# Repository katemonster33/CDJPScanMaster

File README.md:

# CDJPScanMaster

A modern re-design of the Chrysler DRBIII scan tool. This tool, once complete, should be able to connect to 1996(ish) to 2007 vehicles previously supported by the DRB. Most of the key-on-engine-off actuator tests (injector coil and et cetera) should be easy to implement, but the system tests (like Injector Kill) will need special attention to get working.

The user interface for the DRBDBReader (library for interpreting the database.mem) has a UI, but is mostly for my own testing. This library is mostly complete. Initial work on this goes to MWisBest. 

Currently this repo contains a scan tool application, and the beginnings of my new circuit board. This application will not load without the database.mem file found on the DRB III or in the folder of the DRB Emulator. Apparently there's a version of this database shipped with StarScan which theoretically could work, but it's never been tested. The app will soon undergo a complete overhaul, however, as I design a new circuit board which will eventually support Bluetooth, and which will connect to an app for Android and (eventually) PC. This circuit will support ISO9141/KWP2000, SCI(A and B configuration, ECM and TCM), J1850VPW and CCD. 

Credit goes to MWisBest for his initial work on DRBDBReader.

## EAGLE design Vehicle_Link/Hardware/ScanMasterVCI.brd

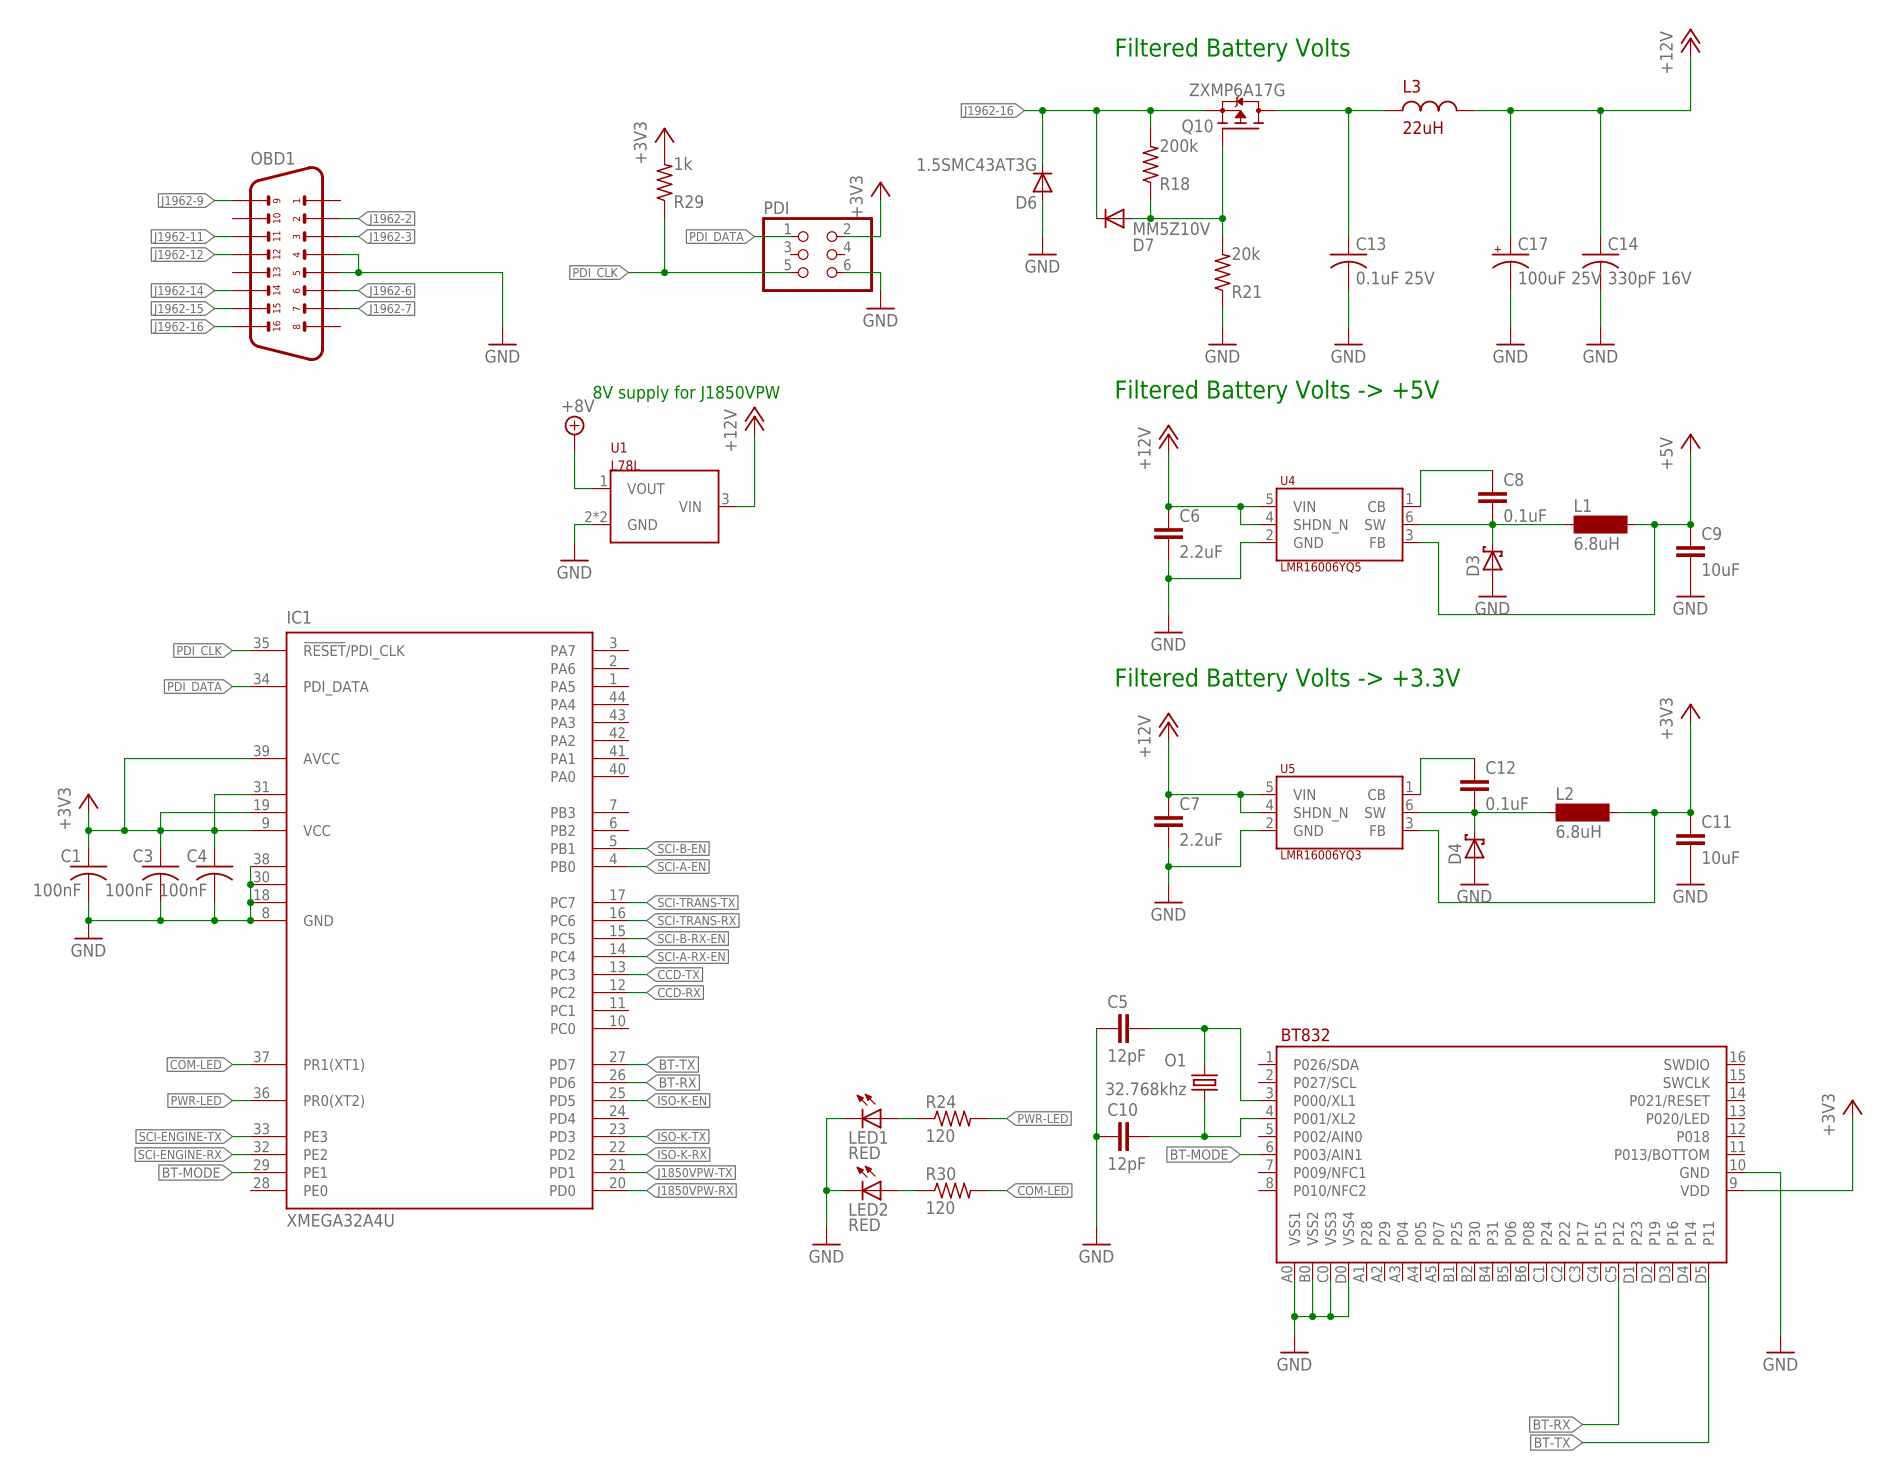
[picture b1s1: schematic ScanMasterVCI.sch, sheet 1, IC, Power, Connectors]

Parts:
C1, C3, C4: 100nF; C0402
C5, C10: 12pF; 0603
C6, C7: 2.2uF; 1206
C8, C12: 0.1uF; 0603
C9, C11: 10uF; 0603
C13: 0.1uF 25V; C0603
C14: 330pF 16V; C0603
C17: 100uF 25V; CPOL-RADIAL-2.5MM-6.5MM
D3, D4: SM5817PL; SOD123FL
D6: 1.5SMC43AT3G; SMC
D7: MM5Z10V; SOD523
IC1: XMEGA32A4U; MLF44-TH
L1, L2: 6.8uH; SM-1206
L3: 22uH; L0603
LED1, LED2: RED; CHIP-LED0603
O1: 32.768khz; FC-135
OBD1: OBD2_OBD2_90; OBD2
PDI: PINHD-2X3; 2X03
Q10: ZXMP6A17G; SOT223
R18: 200k; R0603
R21: 20k; R0603
R24, R30: 120; R0603
R29: 1k; R0603
U1: L78L; SOT89
U4: LMR16006YQ5; SOT6
U5: LMR16006YQ3; SOT6
U6: BT832A

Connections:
+3V3: C1.1, C3.1, C4.1, C11.1, IC1.9 (VCC), IC1.19 (VCC1), IC1.31 (VCC2), IC1.39 (AVCC), L2.2, PDI.2, R29.2, U5.3 (FB), U6.9 (VDD); also elsewhere on the board
+5V: C9.1, L1.2, U4.3 (FB); also elsewhere on the board
+8V: U1.1 (VOUT); also elsewhere on the board
+12V: C6.1, C7.1, C14.1, C17.1 (+), L3.2, U1.3 (VIN), U4.4 (SHDN_N), U4.5 (VIN), U5.4 (SHDN_N), U5.5 (VIN); also elsewhere on the board
BT-MODE: IC1.29 (PE1), U6.6 (P003/AIN1)
BT-RX: IC1.26 (PD6), U6.C5 (P12)
BT-TX: IC1.27 (PD7), U6.D5 (P11)
CCD-RX: IC1.12 (PC2); also elsewhere on the board
CCD-TX: IC1.13 (PC3); also elsewhere on the board
COM-LED: IC1.37 (PR1(XT1)), R30.2
GND: C1.2, C3.2, C4.2, C5.1, C6.2, C7.2, C9.2, C10.1, C11.2, C13.2, C14.2, C17.2 (-), D3.A, D4.A, D6.A, IC1.8 (GND), IC1.18 (GND1), IC1.30 (GND2), IC1.38 (GND3), LED1.C, LED2.C, OBD1.4, OBD1.5, PDI.6, R21.1, U1.2 (GND), U1.2@1 (GND), U4.2 (GND), U5.2 (GND), U6.10 (GND), U6.A0 (VSS1), U6.B0 (VSS2), U6.C0 (VSS3), U6.D0 (VSS4); also elsewhere on the board
ISO-K-EN: IC1.25 (PD5); also elsewhere on the board
ISO-K-RX: IC1.22 (PD2); also elsewhere on the board
ISO-K-TX: IC1.23 (PD3); also elsewhere on the board
J1850VPW-RX: IC1.20 (PD0); also elsewhere on the board
J1850VPW-TX: IC1.21 (PD1); also elsewhere on the board
J1962-2: OBD1.2; also elsewhere on the board
J1962-3: OBD1.3; also elsewhere on the board
J1962-6: OBD1.6; also elsewhere on the board
J1962-7: OBD1.7; also elsewhere on the board
J1962-9: OBD1.9; also elsewhere on the board
J1962-11: OBD1.11; also elsewhere on the board
J1962-12: OBD1.12; also elsewhere on the board
J1962-14: OBD1.14; also elsewhere on the board
J1962-15: OBD1.15; also elsewhere on the board
J1962-16: D6.C, D7.C, OBD1.16, Q10.3 (S), R18.2
unnamed: LED1.A, R24.1
unnamed: C8.1, U4.1 (CB)
unnamed: C8.2, D3.C, L1.1, U4.6 (SW)
unnamed: C12.2, D4.C, L2.1, U5.6 (SW)
unnamed: C12.1, U5.1 (CB)
unnamed: C5.2, O1.2, U6.3 (P000/XL1)
unnamed: C13.1, L3.1, Q10.2 (D), Q10.4 (D)
unnamed: D7.A, Q10.1 (G), R18.1, R21.2
unnamed: C10.2, O1.1, U6.4 (P001/XL2)
unnamed: LED2.A, R30.1
PDI_CLK: IC1.35 (!RESET!/PDI_CLK), PDI.5, R29.1
PDI_DATA: IC1.34 (PDI_DATA), PDI.1
PWR-LED: IC1.36 (PR0(XT2)), R24.2
SCI-A-EN: IC1.4 (PB0); also elsewhere on the board
SCI-A-RX-EN: IC1.14 (PC4); also elsewhere on the board
SCI-B-EN: IC1.5 (PB1); also elsewhere on the board
SCI-B-RX-EN: IC1.15 (PC5)
SCI-ENGINE-RX: IC1.32 (PE2); also elsewhere on the board
SCI-ENGINE-TX: IC1.33 (PE3); also elsewhere on the board
SCI-TRANS-RX: IC1.16 (PC6); also elsewhere on the board
SCI-TRANS-TX: IC1.17 (PC7); also elsewhere on the board

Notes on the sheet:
Filtered Battery Volts
Filtered Battery Volts -> +5V
Filtered Battery Volts -> +3.3V
8V supply for J1850VPW

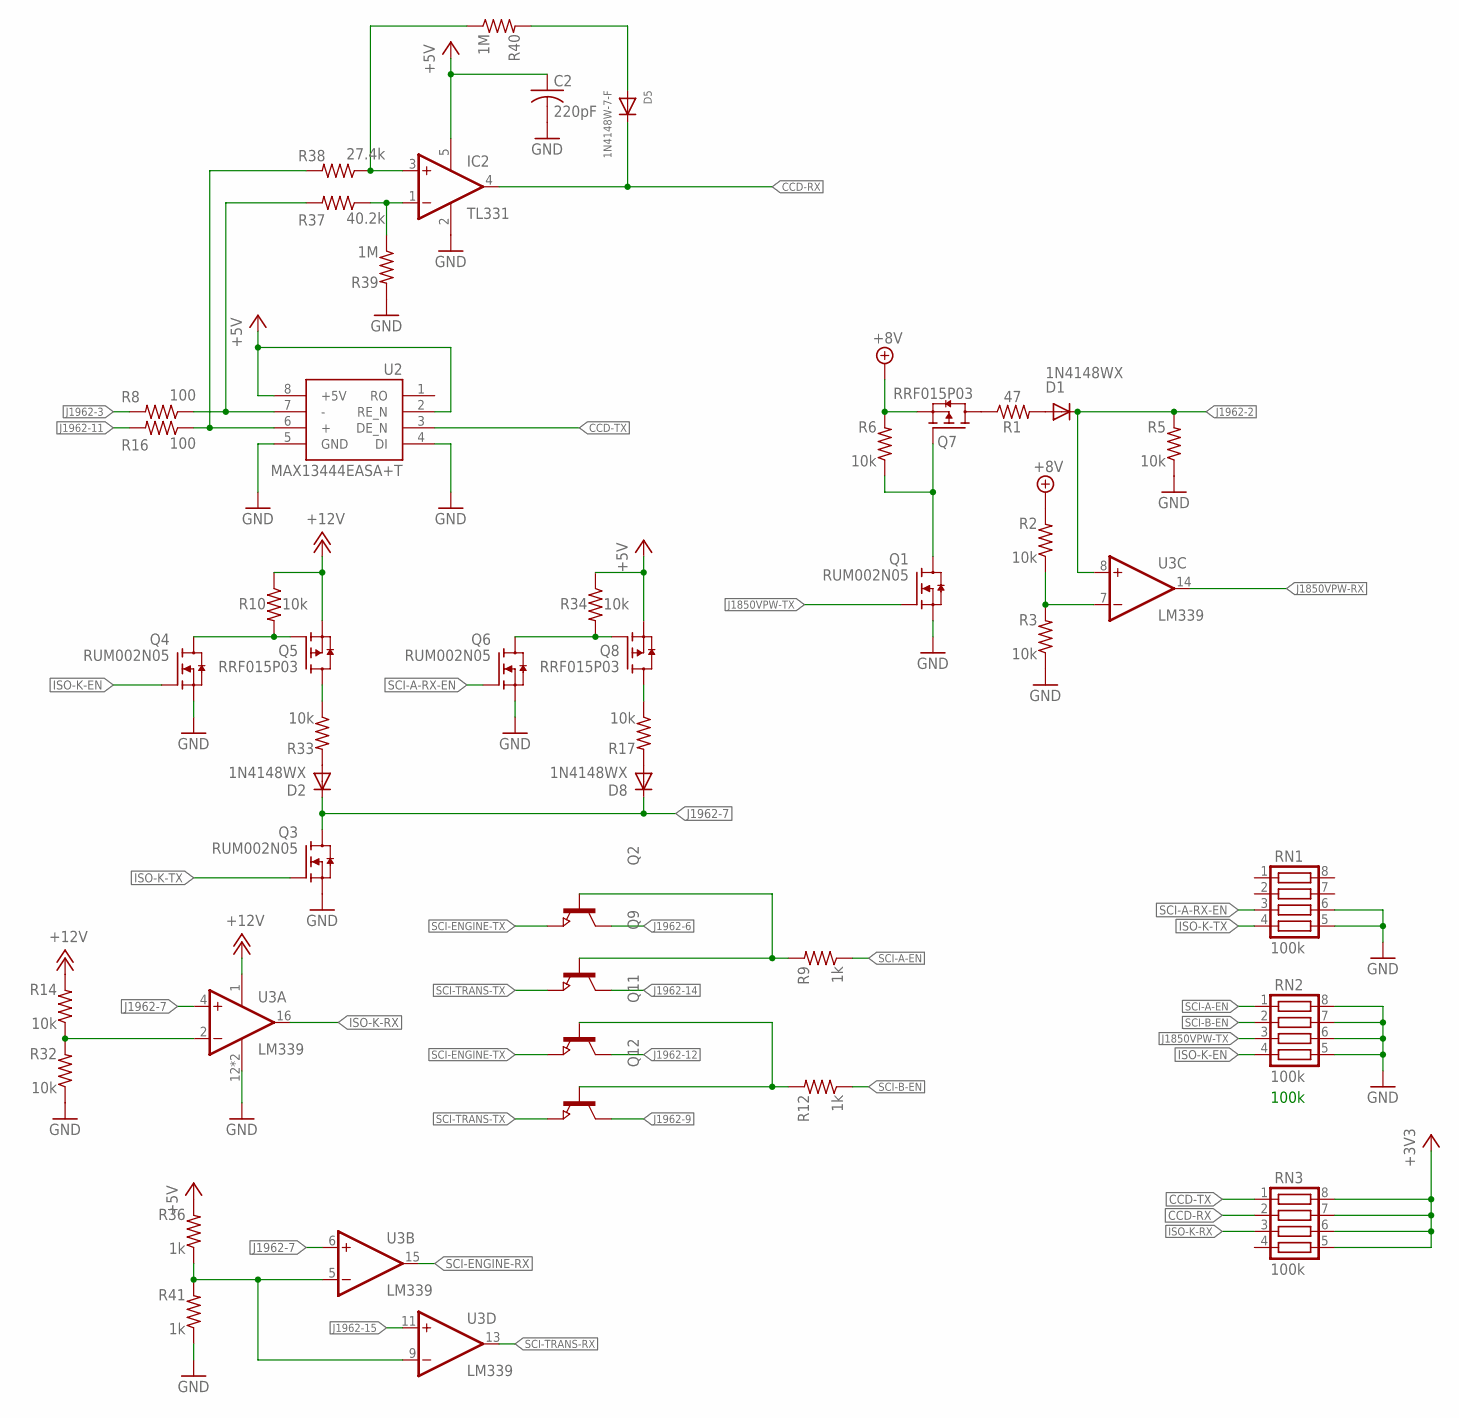
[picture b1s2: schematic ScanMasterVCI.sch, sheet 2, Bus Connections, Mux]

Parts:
C2: 220pF; C0603
D1, D2, D8: 1N4148WX; SOD323-R
D5: 1N4148W-7-F; SOD123FL
IC2: TL331; DBV-R-PDSO-G5
Q1, Q3, Q4, Q6: RUM002N05; EMT3
Q2, Q9, Q11, Q12: NPN-TRANSISTOR_SOT23; SOT23
Q5, Q7, Q8: RRF015P03; SOT323
R1: 47; R0603
R2, R3, R5, R6, R10, R14, R17, R32, R33, R34: 10k; R0603
R8, R16: 100; R0603
R9, R12, R36, R41: 1k; R0603
R37: 40.2k; R0603
R38: 27.4k; R0603
R39, R40: 1M; R0603
RN1, RN2, RN3: 100k; CTS742C083
U2: MAX13444EASA+T; SO08
U3: LM339; QFN16

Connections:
+3V3: RN3.5, RN3.6, RN3.7, RN3.8; also elsewhere on the board
+5V: C2.1, IC2.5 (V+), Q8.2 (S), R34.1, R36.2, U2.2 (RE_N), U2.8 (+5V); also elsewhere on the board
+8V: Q7.2 (S), R2.2, R6.2; also elsewhere on the board
+12V: Q5.2 (S), R10.1, R14.2, U3.1 (V+); also elsewhere on the board
CCD-RX: D5.C, IC2.4 (OUT), RN3.2; also elsewhere on the board
CCD-TX: RN3.1, U2.3 (DE_N); also elsewhere on the board
GND: C2.2, IC2.2 (GND), Q1.2 (S), Q3.2 (S), Q4.2 (S), Q6.2 (S), R3.1, R5.1, R32.1, R39.2, R41.1, RN1.5, RN1.6, RN2.5, RN2.6, RN2.7, RN2.8, U2.4 (DI), U2.5 (GND), U3.12 (V-), U3.PAD (V-); also elsewhere on the board
ISO-K-EN: Q4.1 (G), RN2.4; also elsewhere on the board
ISO-K-RX: RN3.3, U3.16 (OUT); also elsewhere on the board
ISO-K-TX: Q3.1 (G), RN1.4; also elsewhere on the board
J1850VPW-RX: U3.14 (OUT); also elsewhere on the board
J1850VPW-TX: Q1.1 (G), RN2.3; also elsewhere on the board
J1962-2: D1.C, R5.2, U3.8 (+IN); also elsewhere on the board
J1962-3: R8.2; also elsewhere on the board
J1962-6: Q2.3 (C); also elsewhere on the board
J1962-7: D2.C, D8.C, Q3.3 (D), U3.4 (+IN), U3.6 (+IN); also elsewhere on the board
J1962-9: Q12.3 (C); also elsewhere on the board
J1962-11: R16.2; also elsewhere on the board
J1962-12: Q11.3 (C); also elsewhere on the board
J1962-14: Q9.3 (C); also elsewhere on the board
J1962-15: U3.11 (+IN); also elsewhere on the board
unnamed: Q2.1 (B), Q9.1 (B), R9.2
unnamed: Q4.3 (D), Q5.1 (G), R10.2
unnamed: Q11.1 (B), Q12.1 (B), R12.2
unnamed: R36.1, R41.2, U3.5 (-IN), U3.9 (-IN)
unnamed: R14.1, R32.2, U3.2 (-IN)
unnamed: Q7.3 (D), R1.1
unnamed: D2.A, R33.2
unnamed: D8.A, R17.2
unnamed: Q5.3 (D), R33.1
unnamed: Q6.3 (D), Q8.1 (G), R34.2
unnamed: Q1.3 (D), Q7.1 (G), R6.1
unnamed: D1.A, R1.2
unnamed: Q8.3 (D), R17.1
unnamed: R16.1, R38.2, U2.6 (+)
unnamed: IC2.1 (-IN), R37.1, R39.1
unnamed: IC2.3 (+IN), R38.1, R40.1
unnamed: D5.A, R40.2
unnamed: R2.1, R3.2, U3.7 (-IN)
unnamed: R8.1, R37.2, U2.7 (-)
SCI-A-EN: R9.1, RN2.1; also elsewhere on the board
SCI-A-RX-EN: Q6.1 (G), RN1.3; also elsewhere on the board
SCI-B-EN: R12.1, RN2.2; also elsewhere on the board
SCI-ENGINE-RX: U3.15 (OUT); also elsewhere on the board
SCI-ENGINE-TX: Q2.2 (E), Q11.2 (E); also elsewhere on the board
SCI-TRANS-RX: U3.13 (OUT); also elsewhere on the board
SCI-TRANS-TX: Q9.2 (E), Q12.2 (E); also elsewhere on the board

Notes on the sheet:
100k

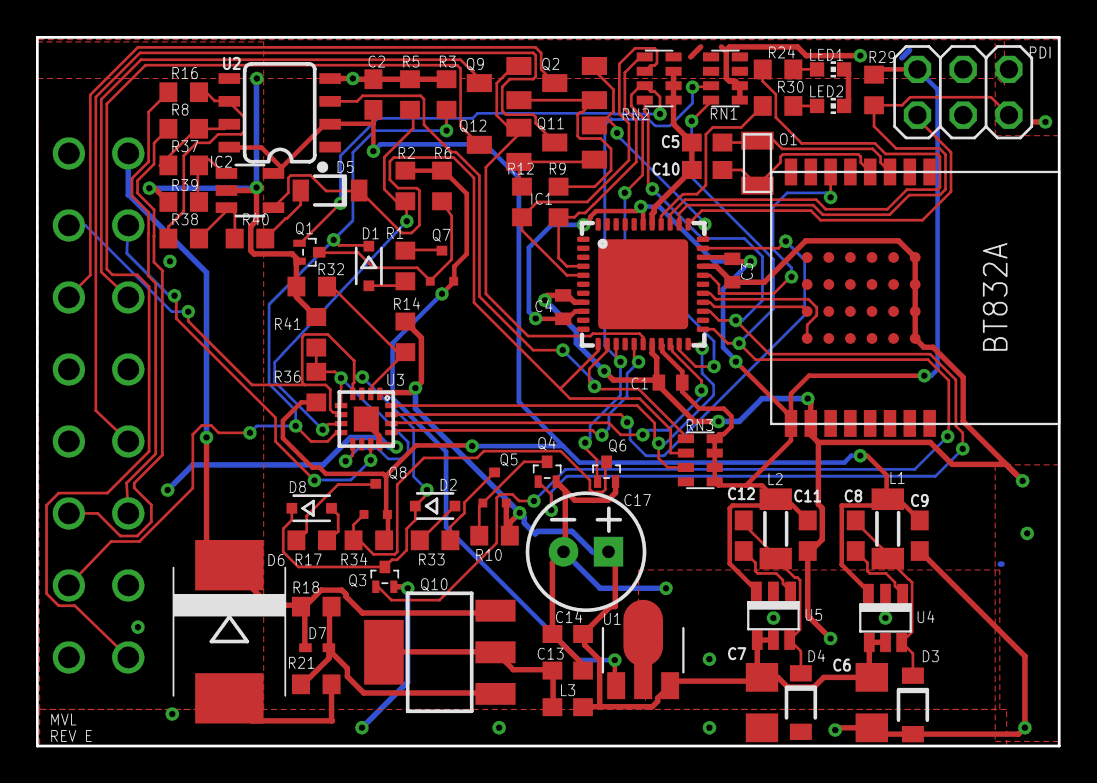
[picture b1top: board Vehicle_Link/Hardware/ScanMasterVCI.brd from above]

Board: 2 copper layers, 56.8 x 39.4 mm, 80 parts (0 on the bottom side), 65 nets.

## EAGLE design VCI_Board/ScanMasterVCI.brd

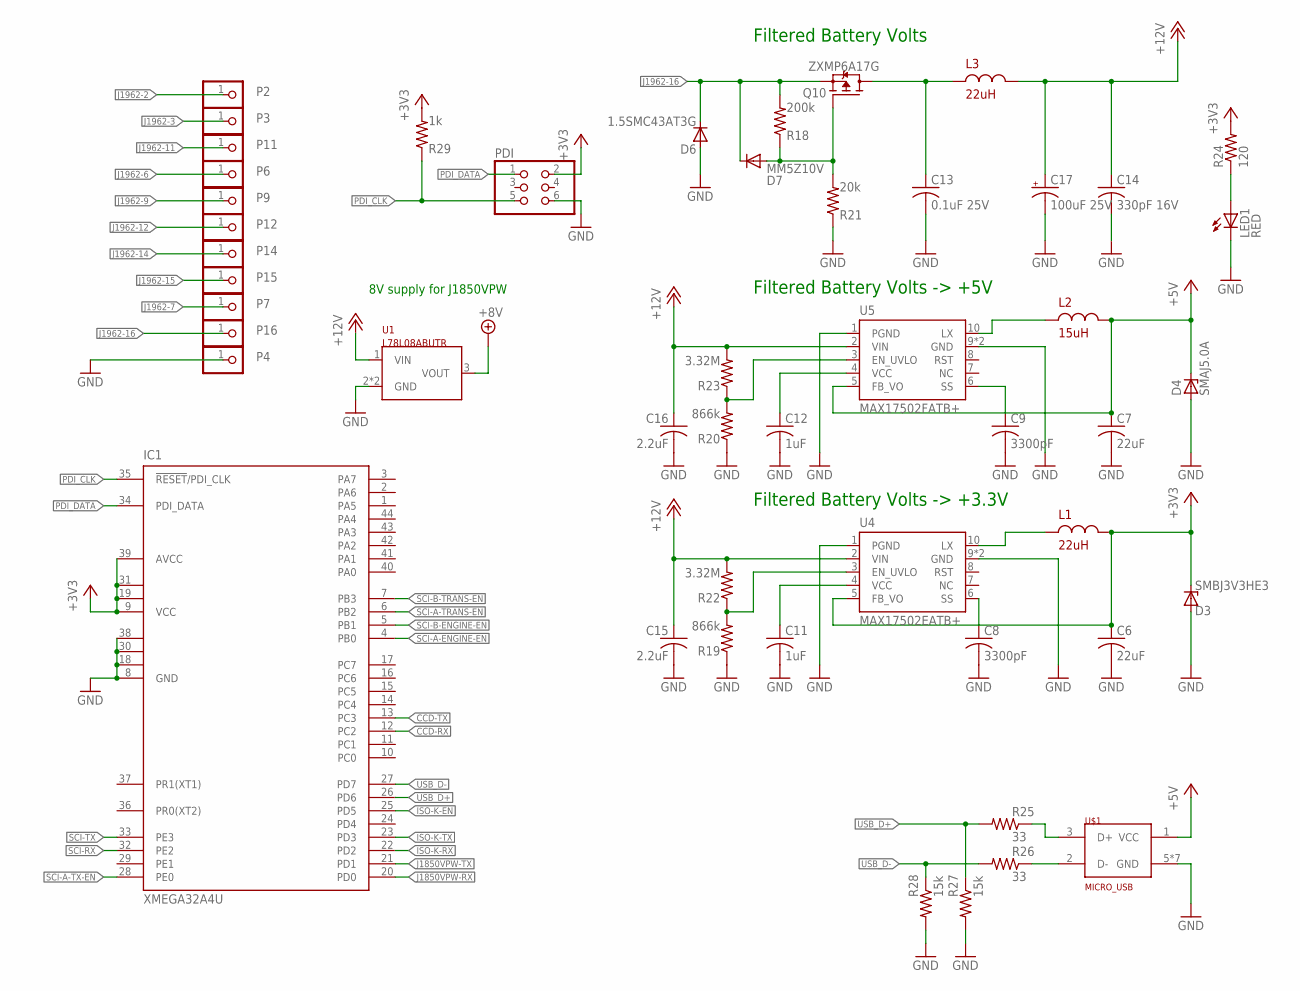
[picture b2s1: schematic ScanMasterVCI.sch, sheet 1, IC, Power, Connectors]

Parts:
C6, C7: 22uF; C0603
C8, C9: 3300pF; C0603
C11, C12: 1uF; C0603
C13: 0.1uF 25V; C0603
C14: 330pF 16V; C0603
C15, C16: 2.2uF; C0603
C17: 100uF 25V; CPOL-RADIAL-2.5MM-6.5MM
D3: SMBJ3V3HE3; SMB
D4: SMAJ5.0A; SMB
D6: 1.5SMC43AT3G; SMC
D7: MM5Z10V; SOD523
IC1: XMEGA32A4U; TQFP44
L1, L3: 22uH; L0603
L2: 15uH; L0603
LED1: RED; CHIP-LED0603
P2, P3, P4, P6, P7, P9, P11, P12, P14, P15, P16: PINHD-1X1; 1X01
PDI: PINHD-2X3; 2X03
Q10: ZXMP6A17G; SOT223
R18: 200k; R0603
R19, R20: 866k; R0603
R21: 20k; R0603
R22, R23: 3.32M; R0603
R24: 120; R0603
R25, R26: 33; R0603
R27, R28: 15k; R0603
R29: 1k; R0603
U1: L78L08ABUTR; SOT89
U4: MAX17502EATB+; TDFN-10-EP
U5: MAX17502FATB+; TDFN-10-EP
U$1: MICRO_USB; 10118192

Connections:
+3V3: C6.1, D3.C, IC1.9 (VCC), IC1.19 (VCC1), IC1.31 (VCC2), IC1.39 (AVCC), L1.2, PDI.2, R24.2, R29.2, U4.5 (FB_VO); also elsewhere on the board
+5V: C7.1, D4.C, L2.2, U5.5 (FB_VO), U$1.1 (VCC); also elsewhere on the board
+8V: U1.3 (VOUT); also elsewhere on the board
+12V: C14.1, C15.1, C16.1, C17.1 (+), L3.2, R22.2, R23.2, U1.1 (VIN), U4.2 (VIN), U5.2 (VIN); also elsewhere on the board
CCD-RX: IC1.12 (PC2); also elsewhere on the board
CCD-TX: IC1.13 (PC3); also elsewhere on the board
GND: C6.2, C7.2, C8.2, C9.2, C11.2, C12.2, C13.2, C14.2, C15.2, C16.2, C17.2 (-), D3.A, D4.A, D6.A, IC1.8 (GND), IC1.18 (GND1), IC1.30 (GND2), IC1.38 (GND3), LED1.C, P4.1, PDI.6, R19.1, R20.1, R21.1, R27.2, R28.2, U1.2 (GND), U1.2@1 (GND), U4.1 (PGND), U4.9 (GND), U4.EPAD (GND), U5.1 (PGND), U5.9 (GND), U5.EPAD (GND), U$1.5 (GND), U$1.M1 (GND), U$1.M2 (GND), U$1.M3 (GND), U$1.M4 (GND), U$1.M5 (GND), U$1.M6 (GND); also elsewhere on the board
ISO-K-EN: IC1.25 (PD5); also elsewhere on the board
ISO-K-RX: IC1.22 (PD2); also elsewhere on the board
ISO-K-TX: IC1.23 (PD3); also elsewhere on the board
J1850VPW-RX: IC1.20 (PD0); also elsewhere on the board
J1850VPW-TX: IC1.21 (PD1); also elsewhere on the board
J1962-2: P2.1; also elsewhere on the board
J1962-3: P3.1; also elsewhere on the board
J1962-6: P6.1; also elsewhere on the board
J1962-7: P7.1; also elsewhere on the board
J1962-9: P9.1; also elsewhere on the board
J1962-11: P11.1; also elsewhere on the board
J1962-12: P12.1; also elsewhere on the board
J1962-14: P14.1; also elsewhere on the board
J1962-15: P15.1; also elsewhere on the board
J1962-16: D6.C, D7.C, P16.1, Q10.3 (S), R18.2
unnamed: LED1.A, R24.1
unnamed: C8.1, U4.6 (SS)
unnamed: R19.2, R22.1, U4.3 (EN_UVLO)
unnamed: C11.1, U4.4 (VCC)
unnamed: L1.1, U4.10 (LX)
unnamed: C12.1, U5.4 (VCC)
unnamed: R20.2, R23.1, U5.3 (EN_UVLO)
unnamed: C9.1, U5.6 (SS)
unnamed: C13.1, L3.1, Q10.2 (D), Q10.4 (D)
unnamed: L2.1, U5.10 (LX)
unnamed: D7.A, Q10.1 (G), R18.1, R21.2
unnamed: R25.1, U$1.3 (D+)
unnamed: R26.1, U$1.2 (D-)
PDI_CLK: IC1.35 (!RESET!/PDI_CLK), PDI.5, R29.1
PDI_DATA: IC1.34 (PDI_DATA), PDI.1
SCI-A-ENGINE-EN: IC1.4 (PB0); also elsewhere on the board
SCI-A-TRANS-EN: IC1.6 (PB2); also elsewhere on the board
SCI-A-TX-EN: IC1.28 (PE0); also elsewhere on the board
SCI-B-ENGINE-EN: IC1.5 (PB1); also elsewhere on the board
SCI-B-TRANS-EN: IC1.7 (PB3); also elsewhere on the board
SCI-RX: IC1.32 (PE2); also elsewhere on the board
SCI-TX: IC1.33 (PE3); also elsewhere on the board
USB_D+: IC1.26 (PD6), R25.2, R27.1
USB_D-: IC1.27 (PD7), R26.2, R28.1

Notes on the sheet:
Filtered Battery Volts
Filtered Battery Volts -> +5V
Filtered Battery Volts -> +3.3V
8V supply for J1850VPW

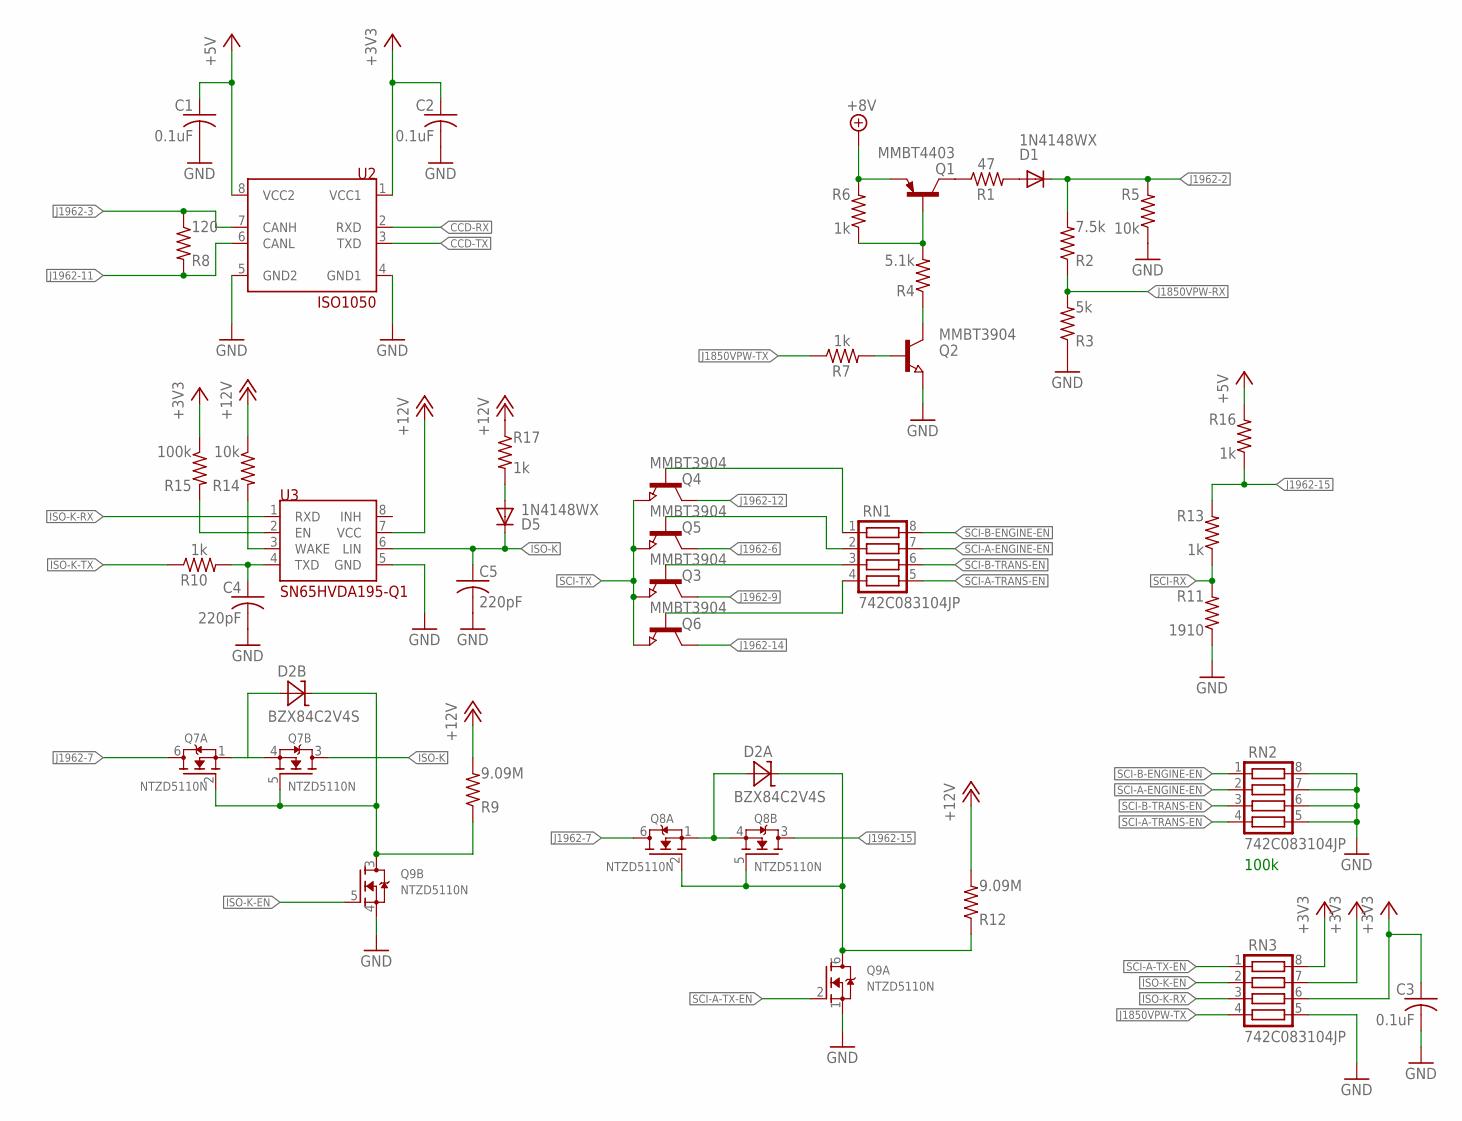
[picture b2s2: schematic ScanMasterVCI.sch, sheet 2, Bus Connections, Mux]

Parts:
C1, C2, C3: 0.1uF; C0603
C4, C5: 220pF; C0603
D1, D5: 1N4148WX; SOD323-R
D2: BZX84C2V4S; SOT363
Q1: MMBT4403; SOT23-BEC
Q2, Q3, Q4, Q5, Q6: MMBT3904; SOT23
Q7, Q8, Q9: NTZD5110N; SOT563
R1: 47; R0603
R2: 7.5k; R0603
R3: 5k; R0603
R4: 5.1k; R0603
R5, R14: 10k; R0603
R6, R7, R10, R13, R16, R17: 1k; R0603
R8: 120; R0603
R9, R12: 9.09M; R0603
R11: 1910; R0603
R15: 100k; R0603
RN1, RN2, RN3: 742C083104JP; CTS742C083
U2: ISO1050; SOP08
U3: SN65HVDA195-Q1; SO08

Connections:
+3V3: C2.1, C3.1, R15.1, RN3.6, RN3.7, RN3.8, U2.1 (VCC1); also elsewhere on the board
+5V: C1.1, R16.2, U2.8 (VCC2); also elsewhere on the board
+8V: Q1.E, R6.2; also elsewhere on the board
+12V: R9.2, R12.2, R14.1, R17.1, U3.7 (VCC); also elsewhere on the board
CCD-RX: U2.2 (RXD); also elsewhere on the board
CCD-TX: U2.3 (TXD); also elsewhere on the board
GND: C1.2, C2.2, C3.2, C4.2, C5.2, Q2.2 (E), Q9.1 (S), Q9.4 (S), R3.1, R5.1, R11.1, RN2.5, RN2.6, RN2.7, RN2.8, RN3.5, U2.4 (GND1), U2.5 (GND2), U3.5 (GND); also elsewhere on the board
ISO-K: C5.1, D5.C, Q7.3 (D), U3.6 (LIN)
ISO-K-EN: Q9.5 (G), RN3.2; also elsewhere on the board
ISO-K-RX: RN3.3, U3.1 (RXD); also elsewhere on the board
ISO-K-TX: R10.1; also elsewhere on the board
J1850VPW-RX: R2.1, R3.2; also elsewhere on the board
J1850VPW-TX: R7.1, RN3.4; also elsewhere on the board
J1962-2: D1.C, R2.2, R5.2; also elsewhere on the board
J1962-3: R8.1, U2.7 (CANH); also elsewhere on the board
J1962-6: Q5.3 (C); also elsewhere on the board
J1962-7: Q7.6 (D), Q8.6 (D); also elsewhere on the board
J1962-9: Q3.3 (C); also elsewhere on the board
J1962-11: R8.2, U2.6 (CANL); also elsewhere on the board
J1962-12: Q4.3 (C); also elsewhere on the board
J1962-14: Q6.3 (C); also elsewhere on the board
J1962-15: Q8.3 (D), R13.2, R16.1; also elsewhere on the board
unnamed: D2.2 (A), Q8.1 (S), Q8.4 (S)
unnamed: D2.5 (A), Q7.1 (S), Q7.4 (S)
unnamed: D2.3 (C), Q8.2 (G), Q8.5 (G), Q9.6 (D), R12.1
unnamed: Q2.1 (B), R7.2
unnamed: R15.2, U3.2 (EN)
unnamed: C4.1, R10.2, U3.4 (TXD)
unnamed: D2.6 (C), Q7.2 (G), Q7.5 (G), Q9.3 (D), R9.1
unnamed: Q4.1 (B), RN1.1
unnamed: R14.2, U3.3 (WAKE)
unnamed: Q5.1 (B), RN1.2
unnamed: Q3.1 (B), RN1.3
unnamed: Q6.1 (B), RN1.4
unnamed: Q2.3 (C), R4.1
unnamed: Q1.B, R4.2, R6.1
unnamed: Q1.C, R1.1
unnamed: D1.A, R1.2
unnamed: D5.A, R17.2
SCI-A-ENGINE-EN: RN1.7, RN2.2; also elsewhere on the board
SCI-A-TRANS-EN: RN1.5, RN2.4; also elsewhere on the board
SCI-A-TX-EN: Q9.2 (G), RN3.1; also elsewhere on the board
SCI-B-ENGINE-EN: RN1.8, RN2.1; also elsewhere on the board
SCI-B-TRANS-EN: RN1.6, RN2.3; also elsewhere on the board
SCI-RX: R11.2, R13.1; also elsewhere on the board
SCI-TX: Q3.2 (E), Q4.2 (E), Q5.2 (E), Q6.2 (E); also elsewhere on the board

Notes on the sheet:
100k

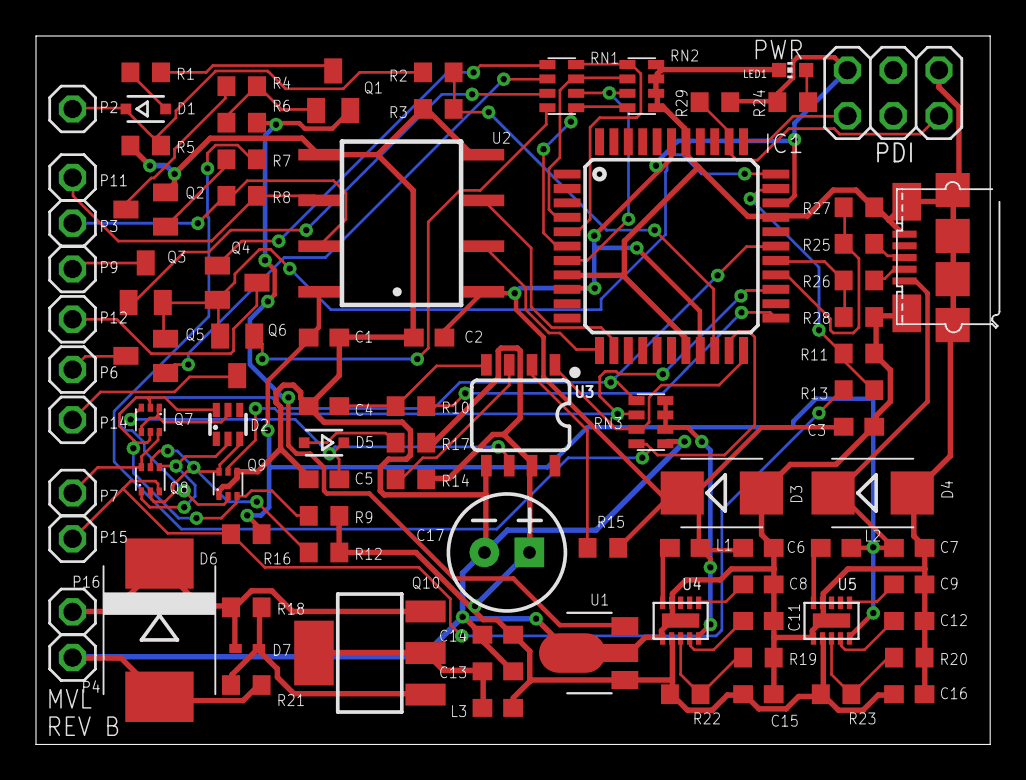
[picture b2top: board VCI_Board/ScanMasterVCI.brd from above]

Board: 2 copper layers, 53.0 x 39.4 mm, 88 parts (0 on the bottom side), 64 nets.

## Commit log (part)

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2017-07-18 Added project's current status.
2017-07-18 Initial code commit.
    note: DRBDBReader is a fork of MWisBest's DRBDBReader.
    CDJPScanMaster is original.
2017-07-21 Added support for engines
    Added all the hooks for trying to identify engines using SCI. Lots of goofy logic, though. Have to start by trying SBECII because of how SCI works, which means extra delays.
    Documents appear to be pretty straight-forward though. Added all the conversions for the mode 16 and mode 2A functions for engine size, year, body style, and ECM style (SBECIII, JTEC, etc). Arduino h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
2017-07-24 Added Arduino code for SCI and CCD
    Added .ino file which (currently) connects to SCI and CCD. Does not allow simultaneous protocol connections.
2017-07-24 Revised support to match current Arduino code
    After making modifications to the Arduino code to handle multiple protocols, added this support into the C# code to switch between protocols during identification. Arduino doesn't handle all protocol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
2017-07-26 Corrected an issue where floats were parsed in wrong bit order
2017-07-26 Added ToString for the GUI.
2017-07-26 Connection logic finished
    Tested with my Arduino Nano on a 1996 Plymouth. Made up a quick and dirty querying thread to send, and added tabs to the GUI page to try and separate data lists from tests and faults.
    Data looks good on CCD. SCI needs much love. Arduino is sending data way too quick and making the module mad. But, it connects somewhat reliably on CCD and SCI.
2017-08-02 More DataDisplay changes
    Missed a crucial line in adding DataDisplay support...should be finished now.
2017-08-02 Moving UI-related stuff out of QueryThread
    The UI stuff that QueryThread does causes all sorts of grief. Moving it out so I can eventually split off all communcation stuff.
2017-08-03 Added TextBoxLogger for serial, stabilizing SCI
    Added a class for constantly updating the text box log periodically. This class is thread-safe, so multiple threads can call this whether in GUI thread or not, without fear of things blowing up.
    Fixed SCI support, at least mostly. Was not respecting timing stuff when sending mode 12. This was causing garbage to show up when trying to request data. Data seems nearly usable now.
2017-08-03 Somehow this change didn't get sent.
2017-08-07 Continuing to strip down Form1 and move pieces into new classes
    Added StaticConverters XML for converting standard SCI and CCD datas into more easily understood strings, for use by the GUI. Added a VehicleLinkManager to keep all PC->Arduino comm code separate fro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
2017-12-11 After much hiatus, am back to design a VCI. I've decided to go with the ATXMEGA16 for my AVR, and code all the protocol support using only current production ICs, which means most of the protocols I 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
2017-12-11 Added circuits for +3.3V and for J1850 power. J1850 needs a very specific voltage and it can vary based on the input. 5V still to come. I've also included the EAGLE library file I'm using to track th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
2017-12-12 Finished re-working CCD. RX line should not be based off the RS485 input, so collision detection can be implemented
2017-12-13 Modified J1850 based on power findings
    Scope shows ~7.3V for high signals. Unsure if current RX circuit is sufficient to drive that down to 3.3 volts. Still looking into more elegant solution.
2017-12-15 Re-worked J1850-RX. Removed dependency on the specialty power circuit. We'll just use 5V to drive VPW high.
2017-12-20 Added SCI RX/TX circuits. Added +5V. Added filtered battery voltage circuit. Added transistors to SCI pins for rudimentary multiplexing. Removed ISO9141 circuitry in favor of an off-the-shelf LIN con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
2017-12-21 Updated to reflect the actual current state of this repo
2017-12-22 Re-did SCI, added activatable ISO9141 pull-up resistor. Based on what I've learned of SCI and how the ECU wiring is done, I've removed all the level shifting from 5V->3.3V, because the bus can be dri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
2017-12-28 Capacitors had reversed polarity. Corrected.
2017-12-29 Re-wrote ISO9141 pull-up, J1850VPW circuit. ISO9141 pull-up resistor activation works on ISO-K-EN line now, removing the need for ISO-K-PULLUP-EN-INV line. However, it requires a double-transistor to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
2017-12-29 Added MOSFETs for muxing. Adding transistors and diodes to protect SCI from the ISO9141 voltage was getting tedious, so I've implemented proper multiplexing using 2 MOSFET IC's I've seen used before.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
2017-12-30 Added routing. Autorouter was able to route 100%, so I went ahead and committed the board with the traces.
2017-12-30 Had to change inductors. Inductor package I was using apparently has no basis in reality. Switched it out for a standard 0603.
2017-12-31 Centered the OBD-II "header" pins on the board. Had to move a ton of stuff around to accomodate moving the OBD-II header to the center of the board, but I am now back to auto-router able to 100% rout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
2018-01-02 Changed OBD2 connector, refined layout
    Decided that it'd be more efficient if I removed all un-used OBD-II pins. Axed about 5 pins and changed the order such that the layout is easier. Managed to get the number of vias down to 68 or so. S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
2018-01-04 Replaced NDC7002N with NTZD5110N
    NDC7002N is out of stock at Digikey, so I am substituting the NTZD5110N. Should be fine, the 5110 just has a lower amp rating than the 7002.
2018-01-08 Widened +12V trace, re-named pins
    I had ran a part renaming script before and forgot to change the names of the OBD pins back to what they're supposed to be.
    I'm not sure if it's necessary, but I'm making the trace for the +12v rail significantly wider, since it will carry the most current. At this point I'm unsure if I need to do this to the 3.3 and 5v r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
2018-01-08 Fixed an erroneous pin assignment. The MAX17502 as I specified it had the bottom exposed pad connected to a random pin, when it should be ground. Fixed. Besides that, mostly small changes, prepping f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
2018-01-10 Added the bill of materials
    First revision of bill of materials.
2018-01-26 Fixed some trace widths
    Some traces that technically carry 12v were sized as non-power traces. Fixed this.
2018-01-26 Widened more traces
    Noticed more power traces technically carrying 3.3V and 5V power that were too thin. Widened these.
2018-01-31 Added extra protection and pull-down resistors to USB circuit, added a pull-up resistor to PDI circuit.
2018-02-02 Some final tweaks before sending out. USB data wires from XMEGA were reversed, fixed. Some small nit-picks with power nets, other than that, it is done. Ordering another set of boards.
2018-02-03 Re-organized directories so I can start committing AVR code. Deleted "VCI_Board" directory, added "Vehicle_Link" since this will be the directory for the whole project. Added a sub-directory for Hard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
2018-02-04 Change was missed somehow
2018-02-12 Added LED. Fixed soldering issues. 8V IC pins were wrong.
    Added an LED for comm indication. Added resistor for this LED. The L78L pinout had VIN and VOUT swapped somehow, fixed this. The MAX17502 has proven very difficult to solder, even with paste. The pad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
2018-02-17 Moved LED resistors next to LEDs because it made more sense
    LED resistors were next to the XMEGA, moved them just so they'd be next to their respective LEDs, and because it would space out the LEDs more.
    Forgot to mention before, but since the NDC7002N MOSFET is coming back into stock, I've switched two of my MOSFETs back to those, since that's how the original schematic had it.
    Moved around part labels so they weren't overlapping vias.
2018-02-17 Filled in J1850 implementation, started adding USB code
2018-03-12 Fixed clock issues to make USB work.
    Managed to get the board to identify on Windows 10 with the built-in ASF driver. Arduino IDE sees the COM port, and connecting to it with the serial monitor works.
2018-03-16 Updated to work with XMEGA protocol
    All the Arduino communication logic has been updated to talk to the XMEGA. Tested this on my current XMEGA and was able to send messages to the MCU.
2018-03-16 Scrubbed ISO1050 from board, replaced with MAX13444EASA+
    Using the CAN tranceiver was not working with CCD, so I've gone with an RS-485 IC instead. I've tested this IC with CCD and can confirm it works for reading.
    Started the process of removing the device names from the board view, instead I will be showing the values for resistors, capacitors, and inductors, for ease of assembly.
2018-03-16 Finished replacing names with values on the board view. Resistors, capacitors and inductors all should be showing the values instead of the names on the board view. This makes organizing parts for as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
2018-03-17 Added makefile, and a quick script for building/deploying in Linux. Many more changes to SCI, fixed a problem where SCI would never clear its buffer. I've tested SCI, RX and TX both now appear to wor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
2018-03-18 More changes for SCI to make high/low speed function properly.
2018-03-23 Re-write. Fixed SCI. Added ring buffer. Fixed CCD
    SCI tested and working as of yesterday. RX and TX on SCI A Engine was tested with multiplexing as it sits on the board schematic. SCI RX has modifications on the schematic that will be committed shor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
    RX buffer was starting to be a problem with the small program memory of the XMEGA 32A4U, so I implemented a ring buffer of 1024 bytes. This can be adjusted at will depending on whether I need the mem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
    CCD RX has been tested and is working with major changes to the schematic. Commits to come. Testing of TX to come as well.
2018-03-25 Started implementing CCD transmitting
    Started my implementation of CCD message transmission, including respecting bus "collisions" at the electrical level. Currently I only do this for the first byte transmitted.
2018-03-28 Removed a #define from conf_usb.h and modified the common udi_cdc.c to correct a compiler warning
2018-03-28 Set the land pattern of MAX17502 back to what the spec says.
    I recently had an overheating issue with the 5V MAX17502 on the PCB, so I am expanding the land pattern back to the size it was before. I'll simply need to be more diligent when applying solder paste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
2018-03-28 Corrected the 8V IC being the wrong way around. Fixed pull-up resistors.
    Lots of pull-up resistors were 10k, or even 100k, and that doesn't really seem to work in practical cases, so I've corrected them all to be 1k. For CCD, since I had 3 1K resistors close to each other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
2018-03-29 Missed this in last commit. Found issues in USART code, not controlling the correct CTRL register.
2018-04-19 Ditched the MOSFETs. Kept having problems with the MOSFETs, plus they're a pain to solder and expensive, so I designed a much better way of multiplexing between SCI A config and ISO9141, which is to 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
2018-06-28 Forgot a bunch of series resistors for the transistor bases. Also added another transistor to the SCI-RX-7 circuit, to convert the +12v/+5v from pin 7 to +5v into the Arduino.
2019-10-26 Made some landing pad changes to the voltage IC's, to fix heat issues I saw. Started looking into simplifying the circuit to get rid of some of the vias.
2019-10-31 Deleted MOSFETs. They don't appear to work well with ISO9141. I need another way to switch between 5V/12V. Probably going to switch to simple transistors.
2019-11-02 Based on testing I did previously, added new circuits to hopefully finish out the CCD, SCI, and ISO9141. J1850 still needs work.
2019-11-08 CCD RX circuit tested. Don't have the firmware in a state to test the TX but I want to move forward with new boards for testing. I've finished re-laying out the board. Made a minor change to J1850, s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
2019-11-09 Reviewed the CCD circuit and found some small issues with the RX circuit, fixed.
2019-11-18 Started experimenting with MOSFETs, added new parts to the library for the connector I'm planning on using.
2019-11-22 Removed the BJTs I was using. Going to try the schematic with MOSFETs.
2019-11-30 Finally swapped out the USB connector for a Bluetooth module, BT823A. Finished the board layout with minimal changes to the comm circuits. Bumped the rev number to D
2019-12-02 Added OBD connector board section, along with proper connectors so I don't have to solder wires anymore. Still need to add milling marks
2019-12-04 Noticed an issue on the OBD connector. Pins didn't match to main board. Besides that final touches before I order boards, minimized vias and re-routed some traces that were just routed strangely
2020-01-26 Modified firmware for talking to BT832A bluetooth LE module. Did some of the leg work for modifying mux logic to match latest schematic. BLE tested and working.

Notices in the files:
parts and their libraries:
SparkFun-Capacitors: Licensing: Creative Commons ShareAlike 4.0 International - https://creativecommons.org/licenses/by-sa/4.0
